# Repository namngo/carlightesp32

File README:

Formular to calculate vout by R for Mp1584EN:
Vout = (R+8200)/10250

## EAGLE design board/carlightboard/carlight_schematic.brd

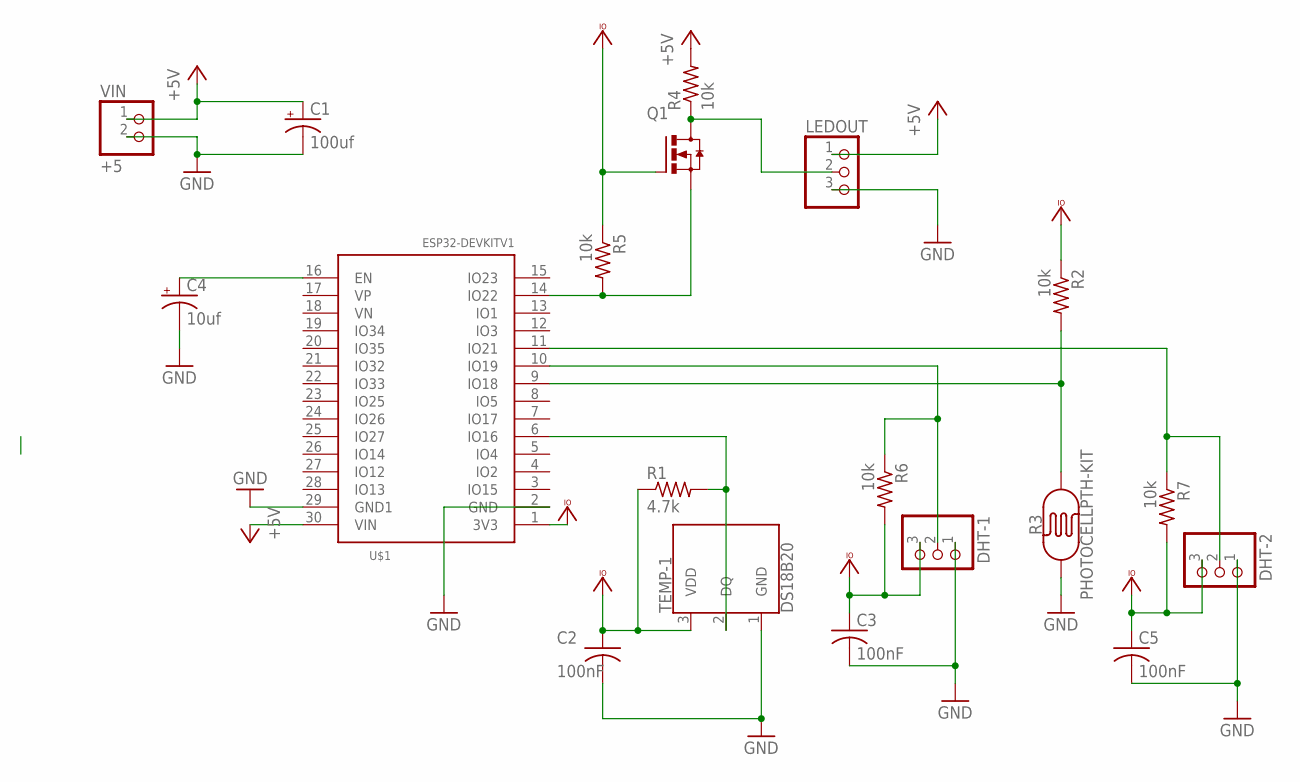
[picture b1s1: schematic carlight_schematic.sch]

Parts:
C1: 100uf; 153CLV-0605
C2, C3, C5: 100nF; C0805
C4: 10uf; 153CLV-0605
DHT-1, DHT-2: PINHD-1X3; 1X03
LEDOUT: PINHD-1X3; 1X03
Q1: 2N7002; SOT23-3
R1: 4.7k; R0805
R2, R4, R5, R6, R7: 10k; R0805
R3: PHOTOCELLPTH-KIT; PHOTOCELL-KIT
TEMP-1: DS18B20; TO-92-AMMO
U$1: ESP32DEVKITV1; ESP32-DEVKITV1
VIN: +5; 1X02

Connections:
+5V: C1.+, LEDOUT.1, R4.2, U$1.30 (VIN), VIN.1
GND: C1.-, C2.2, C3.2, C4.-, C5.2, DHT-1.1, DHT-2.1, LEDOUT.3, R3.1, TEMP-1.1 (GND), U$1.2 (GND), U$1.29 (GND1), VIN.2
unnamed: Q1.2 (S), R5.2, U$1.14 (IO22)
unnamed: R1.2, TEMP-1.2 (DQ), U$1.6 (IO16)
unnamed: LEDOUT.2, Q1.3 (D), R4.1
unnamed: R2.2, R3.2, U$1.9 (IO18)
unnamed: C4.+, U$1.16 (EN)
unnamed: DHT-2.2, R7.1, U$1.11 (IO21)
unnamed: DHT-1.2, R6.1, U$1.10 (IO19)
VCCIO: C2.1, C3.1, C5.1, DHT-1.3, DHT-2.3, Q1.1 (G), R1.1, R2.1, R5.1, R6.2, R7.2, TEMP-1.3 (VDD), U$1.1 (3V3)

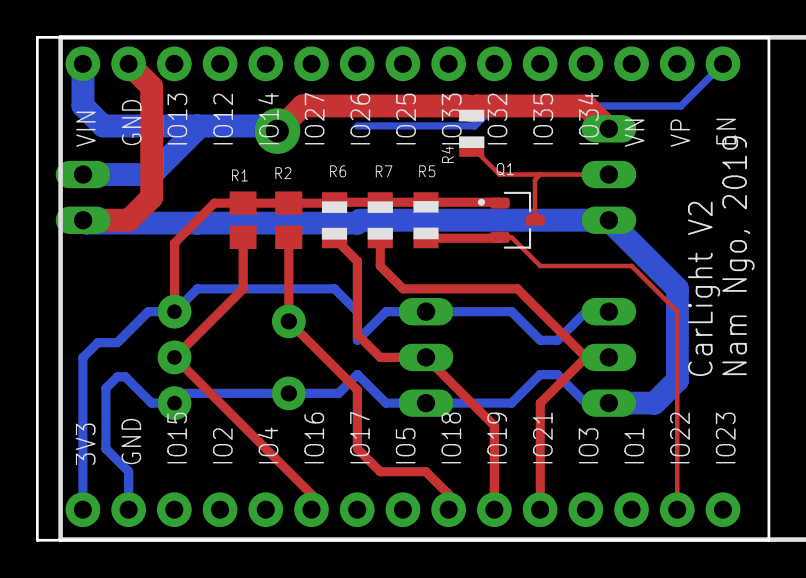
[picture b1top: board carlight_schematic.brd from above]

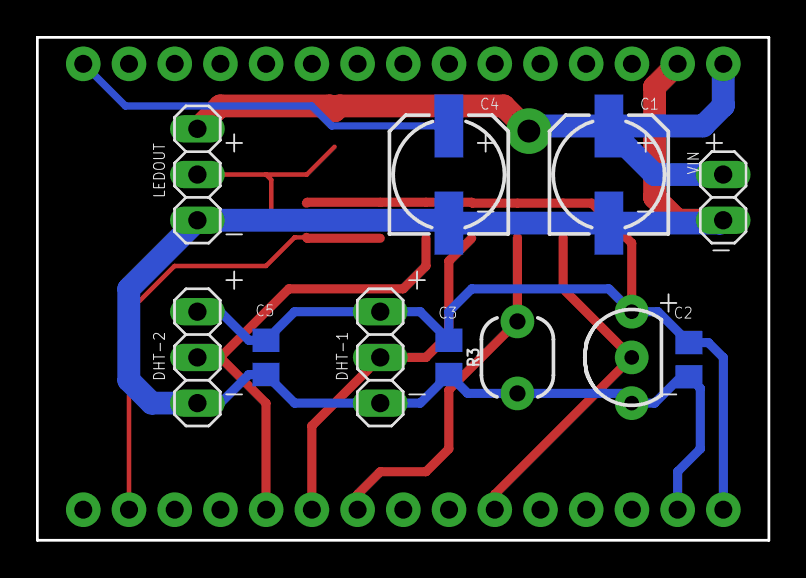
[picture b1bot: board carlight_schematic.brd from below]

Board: 2 copper layers, 40.6 x 27.9 mm, 19 parts (11 on the bottom side), 10 nets.

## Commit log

2019-07-28 Hello world
2019-07-28 Remove browse vc
2019-07-28 add to gitignore
2019-07-29 not working
2019-07-29 new version, not working
2019-07-29 idf tool, not working
2019-07-29 Arduino ftw
2019-07-29 Web server working
2019-07-30 add macos
2019-09-23 add board
2019-09-23 Finish board
2019-10-04 finish temporary
2019-10-06 light api
2019-10-06 refactor espnetwork out
2019-10-07 server
2019-10-07 changes:
2019-10-07 changes - log
2019-10-07 finally work lambda
2019-10-10 update to linux
2019-10-10 double setting light
2019-10-11 about to refactor to classes
2019-10-13 doing sensors
2019-10-13 temp address
2019-10-15 finish sensor and run clang-format
2019-10-16 sensors
2019-10-16 Bootstrap
2019-10-17 layout
2019-10-17 refactoring
2019-10-18 refactor class
2019-10-18 webserver
2019-10-21 web server
2019-10-21 putstring not working
2019-10-21 getting there with the leds
2019-10-21 done with led
2019-10-23 done with light
2019-10-23 temp
2019-10-23 done with sensor
2019-10-23 index
2019-10-24 tweak html
2019-10-24 meta
2019-11-10 update the schematic
2019-11-11 add readme and change sensor
2019-11-11 change how to read dallas
2019-11-11 change value of flash cap to 10uf
2019-11-18 change sensors
2019-11-25 final touch before attaching to car

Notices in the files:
parts and their libraries:
SparkFun-Sensors: Licensing: Creative Commons ShareAlike 4.0 International - https://creativecommons.org/licenses/by-sa/4.0
